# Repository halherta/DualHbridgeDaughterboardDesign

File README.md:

# DualHbridgeDaughterboardDesign

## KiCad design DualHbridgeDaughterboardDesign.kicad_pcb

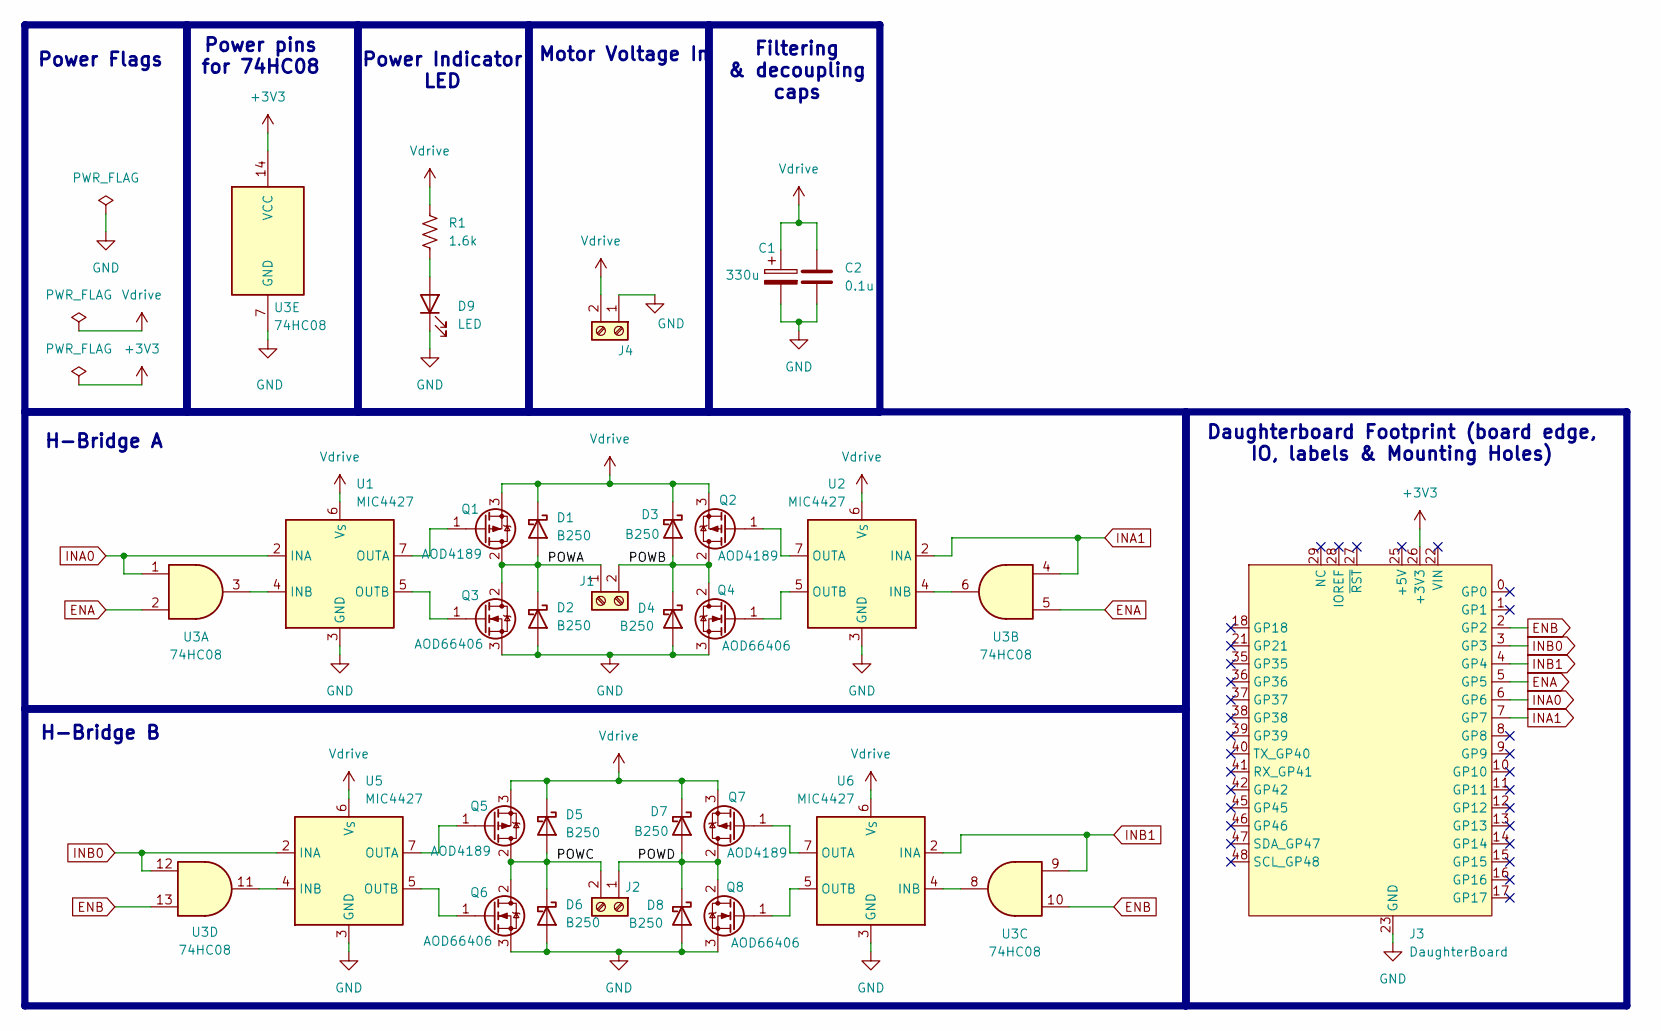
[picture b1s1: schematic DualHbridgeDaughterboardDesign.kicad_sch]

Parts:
C1: 330u; CP_Elec_8x10
C2: 0.1u; C_1206_3216Metric_Pad1.33x1.80mm_HandSolder
D1, D2, D3, D4, D5, D6, D7, D8: B250; D_SMB
D9: LED; LED_1206_3216Metric_Pad1.42x1.75mm_HandSolder
J1, J2, J4: Screw_Terminal_01x02; TerminalBlock_Phoenix_MKDS-1,5-2_1x02_P5.00mm_Horizontal
J3: DaughterBoard; DaughterBoardTemplate
Q1, Q2, Q5, Q7: AOD4189; TO-252-2
Q3, Q4, Q6, Q8: AOD66406; TO-252-2
R1: 1.6k; R_1206_3216Metric_Pad1.30x1.75mm_HandSolder
U1, U2, U5, U6: MIC4427; SO-8_3.9x4.9mm_P1.27mm
U3: 74HC08; SO-14_3.9x8.65mm_P1.27mm

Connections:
+3V3: J3.26 (+3V3), J3.32 (+3V3), U3.14 (VCC)
/POWA: D1.2 (A), D2.1 (K), J1.1, Q1.2 (D), Q3.2 (D)
/POWB: D3.2 (A), D4.1 (K), J1.2, Q2.2 (D), Q4.2 (D)
/POWC: D5.2 (A), D6.1 (K), J2.2, Q5.2 (D), Q6.2 (D)
/POWD: D7.2 (A), D8.1 (K), J2.1, Q7.2 (D), Q8.2 (D)
ENA: J3.5 (GP5), U3.2, U3.5
ENB: J3.2 (GP2), U3.10, U3.13
GND: C1.2, C2.2, D2.2 (A), D4.2 (A), D6.2 (A), D8.2 (A), D9.1 (K), J3.23 (GND), J3.24 (GND), J3.30 (GND), J4.1, Q3.3 (S), Q4.3 (S), Q6.3 (S), Q8.3 (S), U1.3 (GND), U2.3 (GND), U3.7 (GND), U5.3 (GND), U6.3 (GND)
INA0: J3.6 (GP6), U1.2 (INA), U3.1
INA1: J3.7 (GP7), U2.2 (INA), U3.4
INB0: J3.3 (GP3), U3.12, U5.2 (INA)
INB1: J3.4 (GP4), U3.9, U6.2 (INA)
unnamed: D9.2 (A), R1.2
unnamed: Q1.1 (G), U1.7 (OUTA)
unnamed: Q2.1 (G), U2.7 (OUTA)
unnamed: Q3.1 (G), U1.5 (OUTB)
unnamed: Q4.1 (G), U2.5 (OUTB)
unnamed: Q5.1 (G), U5.7 (OUTA)
unnamed: Q6.1 (G), U5.5 (OUTB)
unnamed: Q7.1 (G), U6.7 (OUTA)
unnamed: Q8.1 (G), U6.5 (OUTB)
unnamed: U1.4 (INB), U3.3
unnamed: U2.4 (INB), U3.6
unnamed: U3.11, U5.4 (INB)
unnamed: U3.8, U6.4 (INB)
Vdrive: C1.1, C2.1, D1.1 (K), D3.1 (K), D5.1 (K), D7.1 (K), J4.2, Q1.3 (S), Q2.3 (S), Q5.3 (S), Q7.3 (S), R1.1, U1.6 (V_{S}), U2.6 (V_{S}), U5.6 (V_{S}), U6.6 (V_{S})

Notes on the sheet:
Filtering & decoupling caps
Power Indicator LED
H-Bridge B
Motor Voltage In
Power pins for 74HC08
Power Flags
H-Bridge A
Daughterboard Footprint (board edge, IO, labels & Mounting Holes)

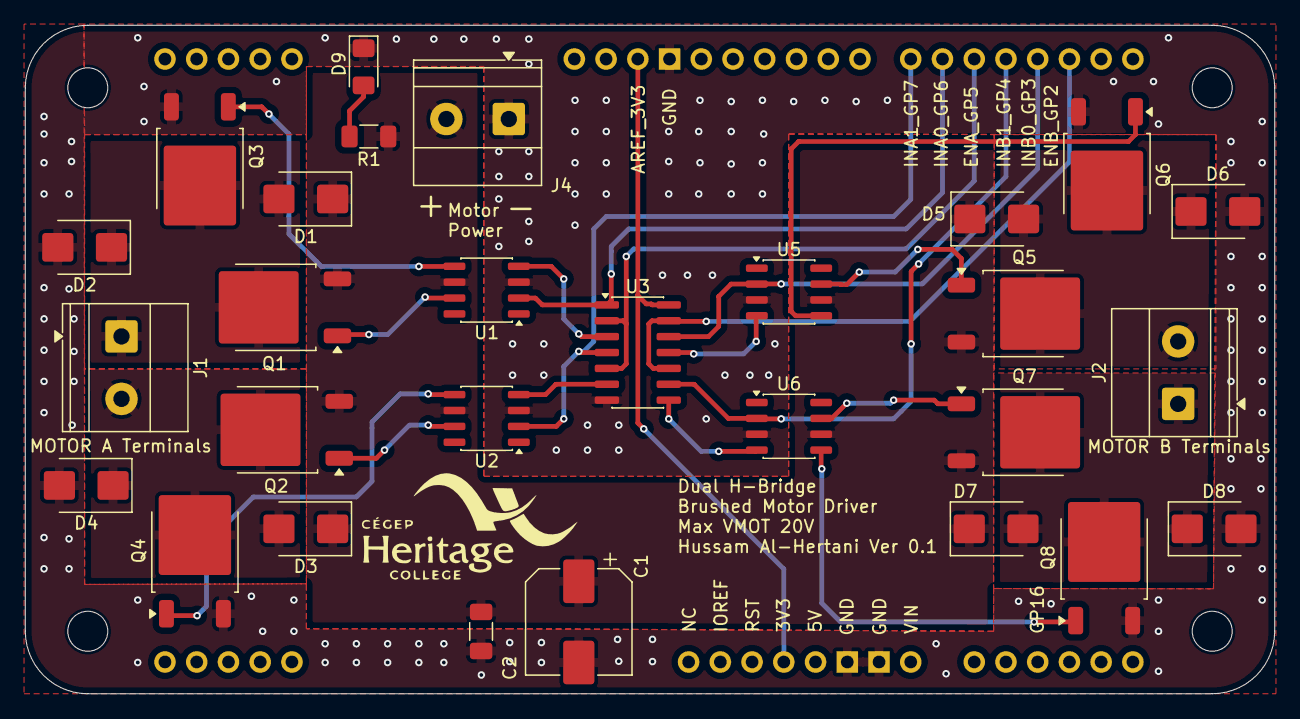
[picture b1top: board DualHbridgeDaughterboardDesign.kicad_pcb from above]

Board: 2 copper layers, 100.0 x 53.5 mm, 29 parts (0 on the bottom side), 26 nets.

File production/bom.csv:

Designator,Footprint,Quantity,Value,LCSC Part #
C1,CP_Elec_8x10,1,330u,
C2,1206,1,0.1u,
"D1, D2, D3, D4, D5, D6, D7, D8",D_SMB,8,B250,
D9,1206,1,LED,
"J1, J2, J4",TerminalBlock_Altech_AK300-2_P5.00mm,3,Screw_Terminal_01x02,
J3,DaughterBoardTemplate,1,DaughterBoard,
"Q1, Q2, Q5, Q7",TO-252-2,4,AOD4189,
"Q3, Q4, Q6, Q8",TO-252-2,4,AOD66406,
R1,1206,1,1.6k,
"U1, U2, U5, U6",SO-8_3.9x4.9mm_P1.27mm,4,MIC4427,
U3,SO-14_3.9x8.65mm_P1.27mm,1,74HC08,

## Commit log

2025-09-30 updated a few things
